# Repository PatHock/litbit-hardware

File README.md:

# litbit-hardware
Eagle schematic, PCB, and libraries

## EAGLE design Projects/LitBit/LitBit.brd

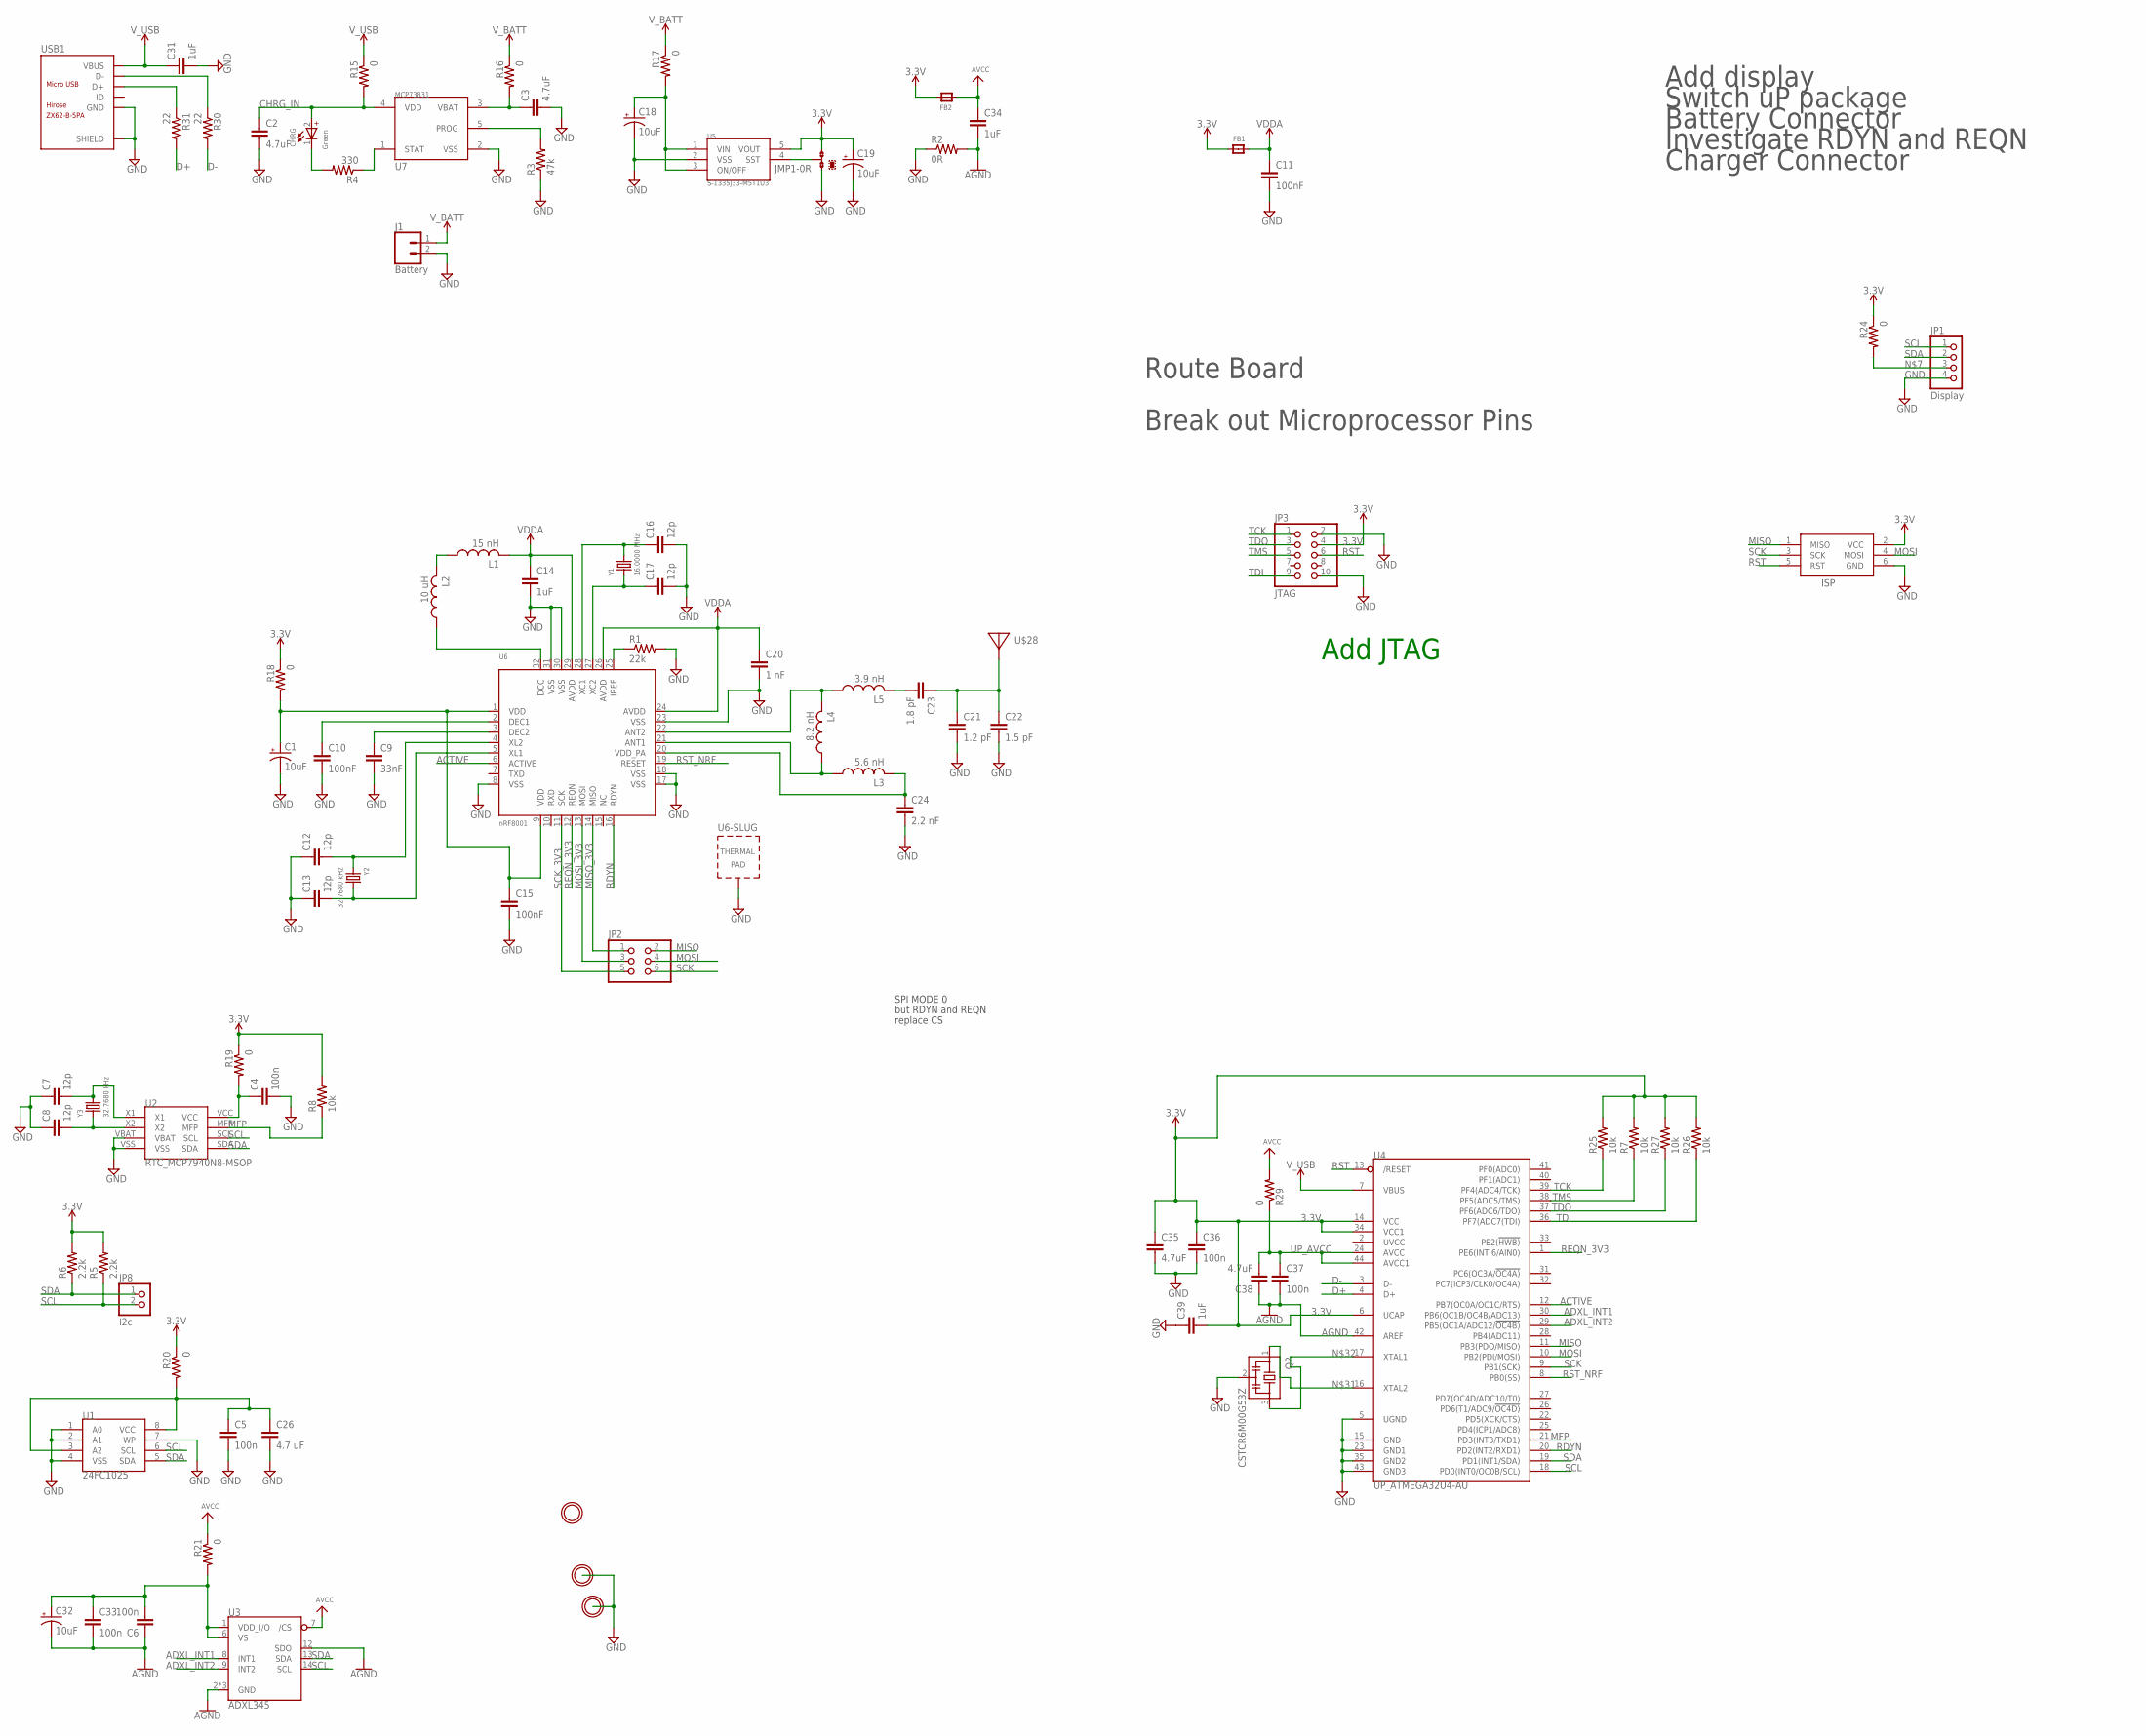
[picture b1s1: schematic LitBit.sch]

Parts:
C1, C18, C19, C32: 10uF; 0603-POLAR
C2, C3, C35, C38: 4.7uF; 0603-CUSTOM
C4, C5, C6, C33, C36, C37: 100n; 0603-CUSTOM
C7, C8, C12, C13, C16, C17: 12p; 0603-CUSTOM
C9: 33nF; 0603-CUSTOM
C10, C11, C15: 100nF; 0603-CUSTOM
C14, C31, C34, C39: 1uF; 0603-CUSTOM
C20: 1 nF; 0603-CUSTOM
C21: 1.2 pF; 0603-CUSTOM
C22: 1.5 pF; 0603-CUSTOM
C23: 1.8 pF; 0603-CUSTOM
C24: 2.2 nF; 0603-CUSTOM
C26: 4.7 uF; 0603-CUSTOM
CHRG: Green; 0603-LED
FB1, FB2: FERRITE; 0603-CUSTOM
GND: MOUNTINGHOLE2.0; MOUNTINGHOLE_2.0_PLATED
ISP: AVRISP-6; AVRISP
J1: Battery; JST-2-SMD
JMP1: 0R-JUMPA; AOR-JMP-0603
JP1: Display; 1X04
JP2: PINHD-2X3; 2X03
JP3: JTAG; 2X05
JP8: I2c; 1X02
L1: 15 nH; 0603-CUSTOM
L2: 10 uH; 0805-CUSTOM
L3: 5.6 nH; 0603-CUSTOM
L4: 8.2 nH; 0603-CUSTOM
L5: 3.9 nH; 0603-CUSTOM
Q2: CSTCR6M00G53Z; CSTCR6M
R1: 22k; 0603-CUSTOM
R2: 0R; 0603-CUSTOM
R3: 47k; 0603-CUSTOM
R4: 330; 0603-CUSTOM
R5, R6: 2.2k; 0603-CUSTOM
R7, R8, R25, R26, R27: 10k; 0603-CUSTOM
R15, R16, R17, R18, R19, R20, R21, R24, R29: 0; 0603-CUSTOM
R30, R31: 22; 0603-CUSTOM
U1: 24FC1025; 8-SOIC_HAND_SOLDER
U2: RTC_MCP7940N8-MSOP; 8-MSOP-CUSTOM
U3: ADXL345; LGA-14
U4: UP_ATMEGA32U4-AU; TQFP44
U5: S-1335J33-M5T1U3; SOT23-5_HAND_SOLDER
U6: nRF8001; QFN32_5MM
U7: MCP73831; SOT23-5_HAND_SOLDER
U$8, U$13: MOUNTINGHOLE2.0; MOUNTINGHOLE_2.0_PLATED
U$28: ANTENNA_PCBNRF8001_1.6MM; ANT_PCB_2.4GHZ_NRF8001_1.6MM_1OZ
USB1: ZX62-B-5PA; MICRO-USB5+6P-SMD-0.65-AB
Y1: 16.0000 MHz; 4-SMD
Y2, Y3: 32.7680 kHz; 2-SMD

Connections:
3.3V: C19.1 (+), C35.1, C36.1, C39.2, FB1.1, FB2.2, ISP.2 (VCC), JMP1.3, JP3.4, R5.2, R6.2, R7.2, R8.2, R18.1, R19.1, R20.1, R24.1, R25.2, R26.2, R27.2, U4.6 (UCAP), U4.14 (VCC), U4.34 (VCC1), U5.5 (VOUT)
ACTIVE: U4.12 (PB7(OC0A/OC1C/RTS)), U6.6 (ACTIVE)
ADXL_INT1: U3.8 (INT1), U4.30 (PB6(OC1B/OC4B/ADC13))
ADXL_INT2: U3.9 (INT2), U4.29 (PB5(OC1A/ADC12/!OC4B))
AGND: C6.1, C32.2 (-), C33.2, C34.2, C37.2, C38.1, R2.2, U3.2 (GND), U3.4 (GND), U3.5 (GND), U3.12 (SDO), U4.42 (AREF)
AVCC: C34.1, FB2.1, R21.1, R29.2, U3.7 (/CS)
CHRG_IN: C2.1, CHRG.2 (+), R15.2, U7.4 (VDD)
D+: R31.2, U4.4 (D+)
D-: R30.2, U4.3 (D-)
GND: C1.2 (-), C2.2, C3.2, C4.2, C5.2, C7.1, C8.1, C9.2, C10.2, C11.2, C12.1, C13.1, C14.2, C15.2, C16.2, C17.2, C18.2 (-), C19.2 (-), C20.2, C21.2, C22.2, C24.2, C26.2, C31.2, C35.2, C36.2, C39.1, ISP.6 (GND), J1.2 (1), JMP1.1, JP1.4, JP3.2, JP3.10, Q2.2, R1.2, R2.1, R3.1, U1.1 (A0), U1.2 (A1), U1.4 (VSS), U1.7 (WP), U2.VBAT, U2.VSS, U4.5 (UGND), U4.15 (GND), U4.23 (GND1), U4.35 (GND2), U4.43 (GND3), U5.2 (VSS), U6.8 (VSS), U6.17 (VSS), U6.18 (VSS), U6.23 (VSS), U6.30 (VSS), U6.31 (VSS), U6.33 (TP), U7.2 (VSS), USB1.5 (GND), USB1.P1 (SHIELD), USB1.P2 (SHIELD), USB1.P3 (SHIELD), USB1.P4 (SHIELD), USB1.P5 (SHIELD), USB1.P6 (SHIELD)
MFP: R8.1, U2.MFP, U4.21 (PD3(INT3/TXD1))
MISO: ISP.1 (MISO), JP2.2, U4.11 (PB3(PDO/MISO))
MISO_3V3: JP2.1, U6.14 (MISO)
MOSI: ISP.4 (MOSI), JP2.4, U4.10 (PB2(PDI/MOSI))
MOSI_3V3: JP2.3, U6.13 (MOSI)
unnamed: C7.2, U2.X1, Y3.P$2 (2)
unnamed: C8.2, U2.X2, Y3.P$1 (1)
unnamed: C10.1, U6.2 (DEC1)
unnamed: C9.1, U6.3 (DEC2)
unnamed: C12.2, U6.4 (XL2), Y2.P$1 (1)
unnamed: C13.2, U6.5 (XL1), Y2.P$2 (2)
unnamed: JP1.3, R24.2
unnamed: C1.1 (+), C15.1, R18.2, U6.1 (VDD), U6.9 (VDD)
unnamed: R30.1, USB1.2 (D-)
unnamed: L1.1, L2.2
unnamed: L2.1, U6.32 (DCC)
unnamed: C16.1, U6.28 (XC1), Y1.P3 (2)
unnamed: JMP1.2, U5.4 (SST)
unnamed: C18.1 (+), R17.2, U5.1 (VIN), U5.3 (ON/OFF)
unnamed: C3.1, R16.2, U7.3 (VBAT)
unnamed: C5.1, C26.1, R20.2, U1.3 (A2), U1.8 (VCC)
unnamed: C17.1, U6.27 (XC2), Y1.P1 (1)
unnamed: C23.2, L5.2
unnamed: L4.2, L5.1, U6.22 (ANT2)
unnamed: L3.1, L4.1, U6.21 (ANT1)
unnamed: R1.1, U6.25 (IREF)
unnamed: C24.1, L3.2, U6.20 (VDD_PA)
unnamed: C21.1, C22.1, C23.1, U$28.FEED
unnamed: CHRG.1 (-), R4.2
unnamed: R3.2, U7.5 (PROG)
unnamed: R4.1, U7.1 (STAT)
unnamed: R31.1, USB1.3 (D+)
unnamed: C4.1, R19.2, U2.VCC
unnamed: Q2.1, U4.16 (XTAL2)
unnamed: Q2.3, U4.17 (XTAL1)
unnamed: C6.2, C32.1 (+), C33.1, R21.2, U3.1 (VDD_I/O), U3.6 (VS)
RDYN: U4.20 (PD2(INT2/RXD1)), U6.16 (RDYN)
REQN_3V3: U4.1 (PE6(INT.6/AIN0)), U6.12 (REQN)
RST: ISP.5 (RST), JP3.6, U4.13 (/RESET)
RST_NRF: U4.8 (PB0(SS)), U6.19 (RESET)
SCK: ISP.3 (SCK), JP2.6, U4.9 (PB1(SCK))
SCK_3V3: JP2.5, U6.11 (SCK)
SCL: JP1.1, JP8.2, R5.1, U1.6 (SCL), U2.SCL, U3.14 (SCL), U4.18 (PD0(INT0/OC0B/SCL))
SDA: JP1.2, JP8.1, R6.1, U1.5 (SDA), U2.SDA, U3.13 (SDA), U4.19 (PD1(INT1/SDA))
TCK: JP3.1, R25.1, U4.39 (PF4(ADC4/TCK))
TDI: JP3.9, R26.1, U4.36 (PF7(ADC7(TDI))
TDO: JP3.3, R27.1, U4.37 (PF6(ADC6/TDO))
TMS: JP3.5, R7.1, U4.38 (PF5(ADC5/TMS))
UP_AVCC: C37.1, C38.2, R29.1, U4.24 (AVCC), U4.44 (AVCC1)
VDDA: C11.1, C14.1, C20.1, FB1.2, L1.2, U6.24 (AVDD), U6.26 (AVDD), U6.29 (AVDD)
V_BATT: J1.1 (2), R16.1, R17.1
V_USB: C31.1, R15.1, U4.7 (VBUS), USB1.1 (VBUS)

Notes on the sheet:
SPI MODE 0
but RDYN and REQN
replace CS
Add JTAG
Route Board
Add display
Break out Microprocessor Pins
Switch uP package
Battery Connector
Charger Connector
Investigate RDYN and REQN

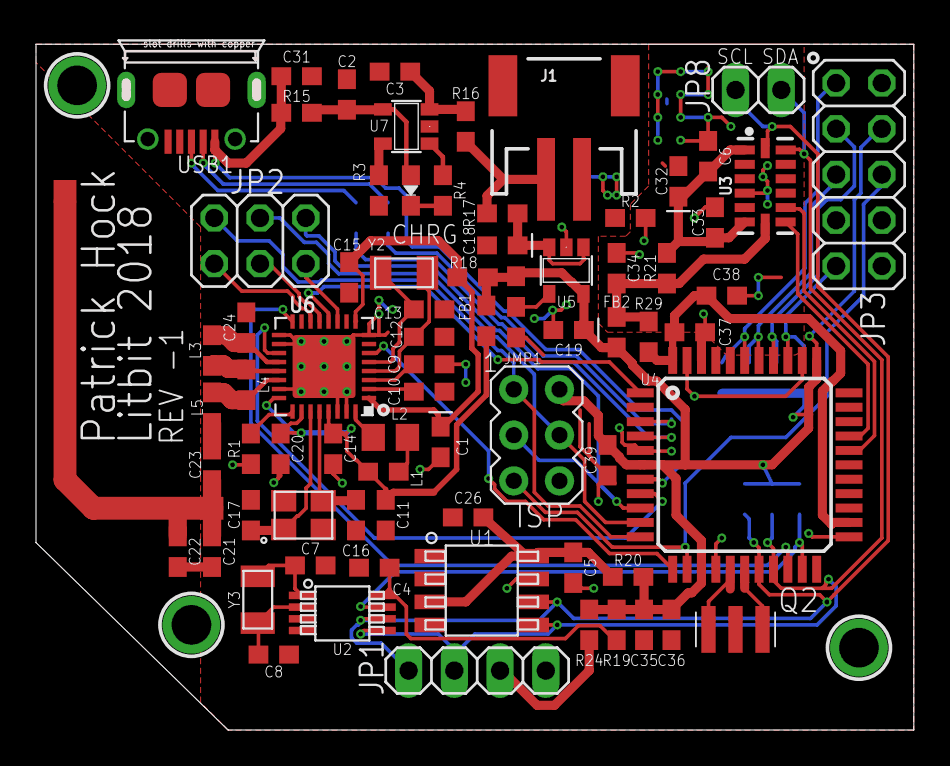
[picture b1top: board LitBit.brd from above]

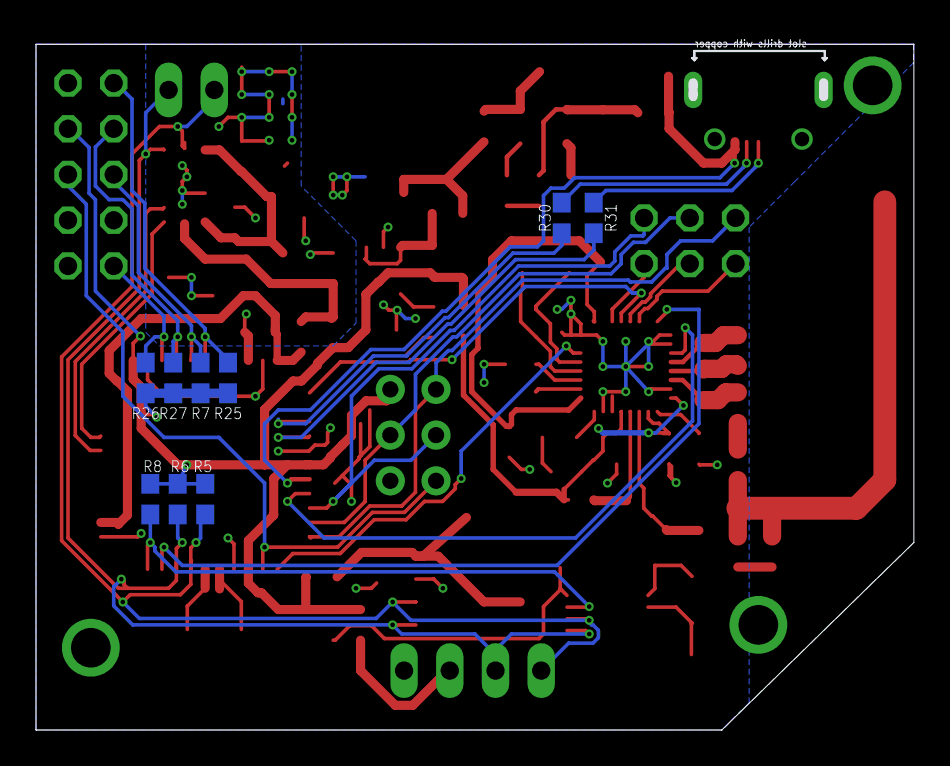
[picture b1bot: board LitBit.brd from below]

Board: 2 copper layers, 48.3 x 38.0 mm, 87 parts (9 on the bottom side), 62 nets.

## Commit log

2018-06-20 change gitignore and add txt files to keep directory structure
2018-06-20 added libraries
2018-06-20 added stuff
2018-06-20 more stuff
2018-06-20 almost milestone
2018-06-20 almost milestoneeeE??
2018-06-21 Change processor package to VQFN to save space.
2018-06-24 Start Layout, change uP package, add display, add JTAG, add battery connector.
2018-06-25 routing, change RTC package
2018-06-26 nearly complete layout
2018-06-26 remove dimension layer text

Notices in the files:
parts and their libraries:
microbuilder: This work is placed in the public domain, and may be freely used for commercial and non-commercial work with the following conditions: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
SparkFun-Connectors: Licensing: Creative Commons ShareAlike 4.0 International - https://creativecommons.org/licenses/by-sa/4.0
